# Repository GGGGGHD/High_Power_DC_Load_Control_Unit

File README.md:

# ⚡ High Power DC Load Control Unit – 2000W | STM32F103

This project features a **2-layer PCB design** that combines both **high-power switching components** and **low-power control circuitry** on a single board. It is built around the **STM32F103 microcontroller** and is capable of driving loads up to **2000W**. The design includes proper isolation techniques to ensure safety, reliability, and performance in high-current environments.

---

## 🔧 Key Features

- ✅ **Microcontroller**: STM32F103C8T6 (ARM Cortex-M3)
- 🔌 **Power Capacity**: Drives loads up to **2000W** (e.g., high-power LEDs, motors, heaters)
- 🛠️ **PCB**: Custom-designed **2-layer board** integrating high and low-power sections
- 🧯 **Isolation**: Implemented electrical isolation and layout techniques for noise immunity and component protection
- 📐 **Design Tools**: KiCad 8.0 used for schematic and PCB layout
- ⚙️ **Peripheral Drivers**: 
  - MOSFET/IGBT gate driver (e.g., UCC5350)
  - Current sensing and thermal monitoring
- 🧪 **Tested and Verified**: Proven control and protection circuitry with real load tests

---

## 📂 Project Structure

```bash
.
├── hardware/
│   ├── schematics.kicad_sch
│   ├── pcb_layout.kicad_pcb
│   ├── 3D_models/
│   └── fabrication_files/
├── firmware/
│   ├── main.c
│   ├── peripherals/
│   └── stm32f103_hal_config/
├── README.md
└── images/
    └── board_render_top.png

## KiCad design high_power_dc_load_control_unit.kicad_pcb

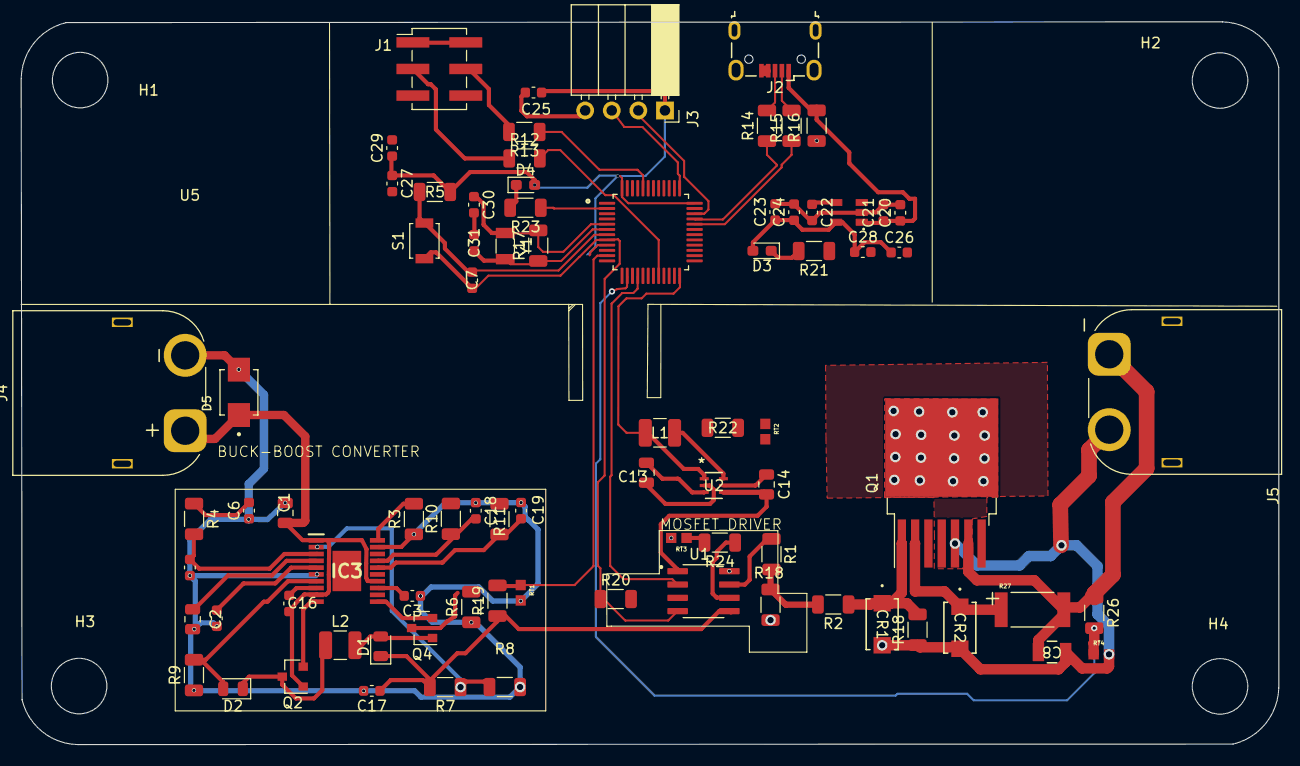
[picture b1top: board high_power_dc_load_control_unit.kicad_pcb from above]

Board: 2 copper layers, 120.1 x 69.0 mm, 85 parts (0 on the bottom side), 52 nets.

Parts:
C1: 10uF; C_0805_2012Metric
C2, C5: 100pF; C_0603_1608Metric
C3: 2.2pF; C_0603_1608Metric
C4: 330nF; C_0805_2012Metric
C6: 2.2nF; C_0603_1608Metric
C7, C20, C26, C27, C28, C29: 105; C_0603_1608Metric
C8: C1206C472K1RECAUTO; CAPC340180_88N_KEM-L
C13: 1uF; C_0805_2012Metric
C14: 22uF; C_0805_2012Metric
C16: 2.2uF; C_0603_1608Metric
C17: 100uF; C_0603_1608Metric
C18, C19: 10nF; C_0603_1608Metric
C21, C24, C25: 104; C_0603_1608Metric
C22: C; C_0603_1608Metric
C23: 106; C_0603_1608Metric
C30, C31: 20p; C_0603_1608Metric
CR1, CR2: SMBJ13CA; DO214AC_LTF-L
D1, D2: D_Schottky; D_0805_2012Metric
D3, D4: LED_Small; LED_0603_1608Metric_Pad1.05x0.95mm_HandSolder
D5: SMBJ40A; DIOM4336X265N
H1, H2, H3, H4: MountingHole; MountingHole_5.3mm_M5
IC3: LT8711EFE#TRPBF; SOP65P640X120-21N
J1: Conn_02x03_Odd_Even; PinHeader_2x03_P2.54mm_Vertical_SMD
J2: USB_B_Micro; USB_Micro-B_Wuerth_629105150521
J3: Conn_01x04_Socket; PinSocket_1x04_P2.54mm_Horizontal
J4, J5: XT60-M; AMASS_XT60PW-M_1x02_P7.20mm_Horizontal
L1: 10uH; L_1210_3225Metric
L2: 4.7uH; L_1210_3225Metric
Q1: IPT007N06N; TO-263-7_TabPin8
Q2: PMOS; SOT-23
Q4: NMOS; SOT-23
R1: 33; R_1206_3216Metric
R2: 4; R_1206_3216Metric
R3: 60.4k; R_1206_3216Metric
R4: 110k; R_1206_3216Metric
R5: 10K; R_1206_3216Metric
R6: 4M; R_1206_3216Metric
R7, R17: 1M; R_1206_3216Metric
R8: 69.8k; R_1206_3216Metric
R9: 4m; R_1206_3216Metric
R10, R11: 10; R_1206_3216Metric
R12, R13: 100K; R_1206_3216Metric
R14, R15: 20; R_1206_3216Metric
R16: 4.7K; R_1206_3216Metric
R18, R18#2, R19, R22, R24, R26: 10k; R_1206_3216Metric
R20: 100; R_1206_3216Metric
R21, R23: 510; R_1206_3216Metric
R27: 3.4; RESC6331X70N
RT1, RT2, RT3, RT4: NCP18XH103F03RB; THRMC1608X95N
S1: GPTS203211B; SW_SPST_B3U-1000P
U1: UCC5350MCD; SOIC127P599X175-8N
U2: LTC3525ESC6-5-TRMPBF; SC70-SC6_LIT-L
U4: RT9193-33GB; SOT94P279X129-5N
U5: STM32F103C8T6; QFP50P900X900X160-48N
Y1: 8MHz; Crystal_SMD_3215-2Pin_3.2x1.5mm

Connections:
/5V: C14.2, U1.1 (VCC1), U2.4 (VOUT)
/*SHDN: C13.2, L1.1, U2.1 (*SHDN), U2.3 (VIN)
/BG: IC3.11 (BG), Q4.2 (G)
/CLAMP: R1.1, U1.7 (CLAMP)
/COIL->diode: D1.2 (A), L2.2, Q4.1 (D)
/CSN: C19.2, IC3.16 (CSN), R11.1
/CSP: C18.2, IC3.17 (CSP), R10.1
/EXTVCC: IC3.15 (EXTVCC), U1.5 (VCC2)
/FB: IC3.2 (FB), R7.1, R8.1
/IN-: R20.2, U1.3 (IN-)
/INTVCC: C3.2, IC3.13 (INTVCC)
/INTVEE: C16.1, IC3.8 (INTVEE)
/ISN: D2.2 (A), IC3.7 (ISN), R9.2
/MCU/5V: U4.1 (VIN), U4.3 (EN)
/MCU/BOOT0: R13.1, U5.44 (BOOT0)
/MCU/BOOT1: R12.2, U5.20 (PB2)
/MCU/BP: C22.1, U4.4 (BP)
/MCU/D+: J2.3 (D+), R14.2, U5.33 (PA12)
/MCU/D-: J2.2 (D-), R15.2, U5.32 (PA11)
/MCU/OSCIN: C30.1, R17.2, U5.5 (PD0_OSC_IN), Y1.2
/MCU/OSCOUT: C31.1, R17.1, U5.6 (PD1_OSC_OUT), Y1.1
/MCU/PA12: R14.1, R16.1
/MCU/RESET: C7.1, R5.1, S1.2, U5.7 (NRST)
/MCU/SWDCLK: J3.3, U5.37 (PA14)
/MCU/SWDIO: J3.2, U5.34 (PA13)
/PMOS_SOURCE: D2.1 (K), L2.1, Q2.3 (S)
/Q1_1: CR1.1, Q1.1, R2.1, R18.2
/R11_2: R6.2, R11.2
/RT: IC3.20 (RT), R3.2
/SS: C4.2, IC3.4 (SS)
/SW: L1.2, U2.6 (SW)
/TG: IC3.10 (TG), Q2.2 (G)
DC-DC_CONV_GND: C1.2, C2.1, C3.1, C4.1, C5.1, C6.1, C17.2, C18.1, C19.1, D5.A, IC3.6 (ISP), IC3.19 (SYNC), R3.1, R6.1, R8.2, R9.1, RT1.2
GNDD: C7.2, C8.1, C13.1, C14.1, C20.1, C20.2, C21.1, C21.2, C22.2, C23.2, C24.2, C25.2, C26.2, C27.2, C28.2, C29.2, CR1.2, CR2.2, IC3.21 (GND), J1.5, J1.6, J2.1 (VBUS), J2.4 (ID), J2.5 (GND), J2.6 (Shield), J3.4, J5.2, Q1.3, R16.2, R18.1, R18#2.2, R20.1, R21.1, R22.1, RT2.2, RT3.2, RT4.2, S1.1, U1.4 (GND1), U1.8 (VEE2), U2.2 (GND), U2.5 (GND), U4.2 (GND), U5.8 (VSSA), U5.23 (VSS), U5.35 (VSS), U5.47 (VSS)
MOS_DRIVE_TRIGGER: R1.2, R2.2, R18#2.1, R24.1, U1.6 (OUT)
MOS_OUT: C8.2, R27.2
NTC_1_OUT: R19.2, RT1.1, U5.11 (PA1)
NTC_2_OUT: R22.2, RT2.1, U5.12 (PA2)
NTC_3_OUT: R24.2, RT3.1, U5.13 (PA3)
NTC_4_OUT: R26.2, RT4.1, U5.14 (PA4)
unnamed: C6.2, R4.1
unnamed: C30.2, C31.2
unnamed: D3.1 (K), R21.2
unnamed: D4.1 (K), R23.2
unnamed: C2.2, IC3.5 (OPMODE)
unnamed: C5.2, IC3.3 (VC), R4.2
unnamed: J1.3, R12.1
unnamed: J1.4, R13.2
PWM_SIGNAL: U1.2 (IN+), U5.16 (PA6)
VCC3V3: C23.1, C24.1, C25.1, C26.1, C27.1, C28.1, C29.1, D3.2 (A), D4.2 (A), J1.1, J1.2, J3.1, R5.2, U4.5 (VOUT), U5.9 (VDDA), U5.24 (VDD), U5.36 (VDD), U5.48 (VDD)
VIN_DC-DC_CONV: C1.1, C16.2, CR2.1, D5.C, IC3.1 (EN/FBIN), IC3.9 (BIAS), IC3.14 (VIN), Q1.2, Q2.1 (D), R27.1
Vout_12V: C17.1, D1.1 (K), R7.2, R19.1

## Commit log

2025-04-03 Added .gitignore to prevent ZIP files from being tracked
2025-04-03 Schematic Almost Completed and PCB Tracing going on
2025-04-03 Update .gitignore to omit Kicad files
2025-04-03 chematics of MCU, Completed in second sheet
2025-04-03 DC-DC Converter Schematics Added
2025-04-03 Added symbols for DC-DC Converter
2025-04-03 Final Commit
2025-04-03 Fix remote issue
2025-04-03 Initial Commit -Uploading project files
2025-04-03 Added new folder with Pictures
